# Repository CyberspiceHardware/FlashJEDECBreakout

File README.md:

# FlashJEDECBreakout

Allows use of SOIC packaged Flash chips in PDIP sockets for Flash, ROM, EPROM etc.

## Jumpers

There are two jumpers:

J1, selects how pin 1 (A14) of the flash part is connected, it can be either to
pin 1 of the header, pin 27 of the header, or omitted to tie it to ground (useful
for replacing 27C128 parts).

J2, selects how pin 26 (~WE) of the flash part is connected, it can be either to
pin 26 of the header, or to VDD.

## Parts list

- U1 - AT28C256E SOIC
- R1 - 3K3 0805 SMT
- J1 - 3 pin 0.1" header
- J2 - 3 pin 0.1" header
- CON1 - 2 x 14 way 0.1" double ended header

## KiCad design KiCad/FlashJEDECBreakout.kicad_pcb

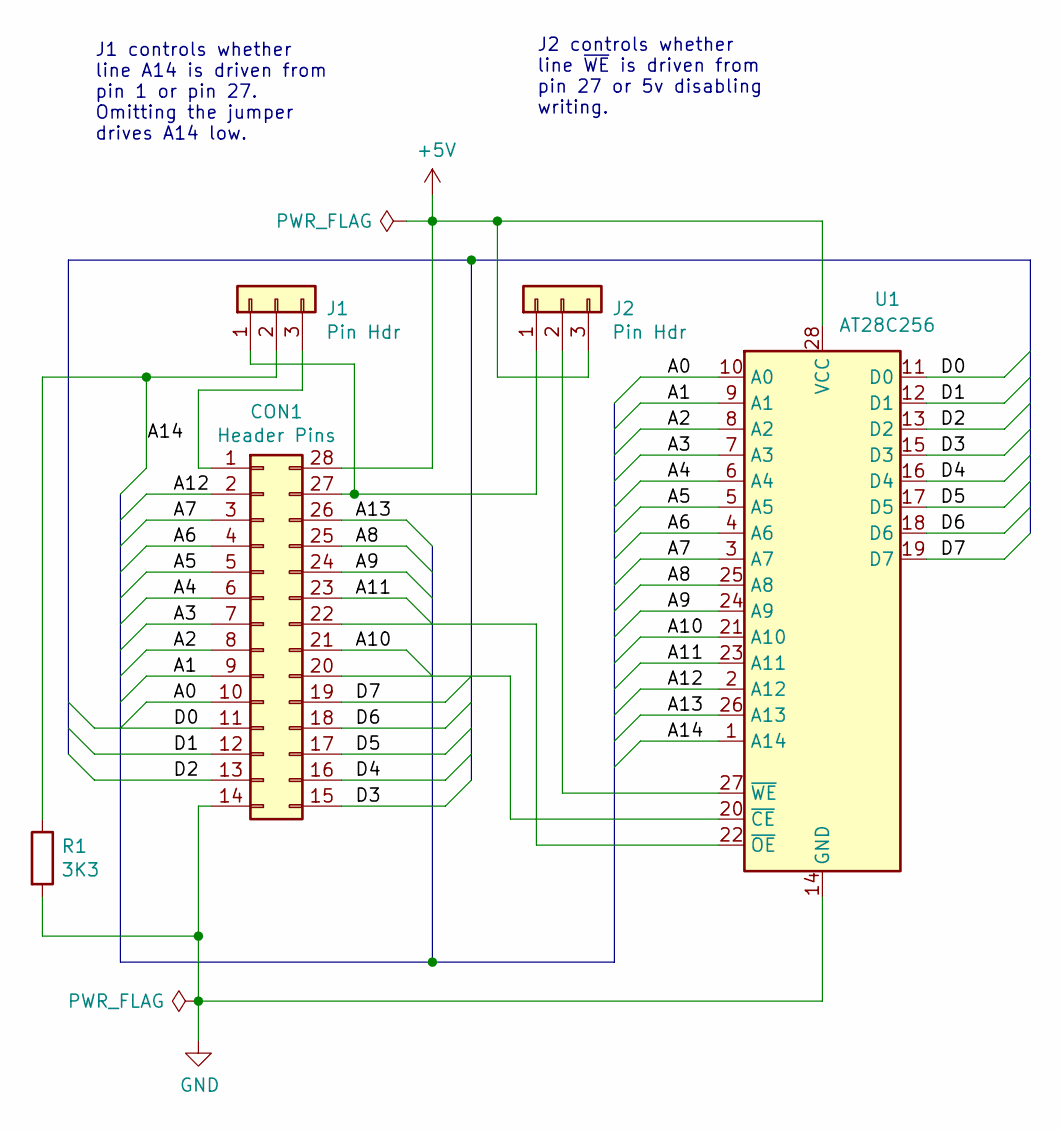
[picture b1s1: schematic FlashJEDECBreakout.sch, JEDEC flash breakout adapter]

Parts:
CON1: Header Pins; DIP-28_W15.24mm_Socket
J1, J2: Pin Hdr; PinHeader_1x03_P2.54mm_Vertical
R1: 3K3; R_0805_2012Metric_Pad1.20x1.40mm_HandSolder
U1: AT28C256; SOIC-28W_7.5x17.9mm_P1.27mm

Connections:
+5V: CON1.28, J2.3, U1.28 (VCC)
/A0: CON1.10, U1.10 (A0)
/A1: CON1.9, U1.9 (A1)
/A2: CON1.8, U1.8 (A2)
/A3: CON1.7, U1.7 (A3)
/A4: CON1.6, U1.6 (A4)
/A5: CON1.5, U1.5 (A5)
/A6: CON1.4, U1.4 (A6)
/A7: CON1.3, U1.3 (A7)
/A8: CON1.25, U1.25 (A8)
/A9: CON1.24, U1.24 (A9)
/A10: CON1.21, U1.21 (A10)
/A11: CON1.23, U1.23 (A11)
/A12: CON1.2, U1.2 (A12)
/A13: CON1.26, U1.26 (A13)
/A14: J1.2, R1.1, U1.1 (A14)
/D0: CON1.11, U1.11 (D0)
/D1: CON1.12, U1.12 (D1)
/D2: CON1.13, U1.13 (D2)
/D3: CON1.15, U1.15 (D3)
/D4: CON1.16, U1.16 (D4)
/D5: CON1.17, U1.17 (D5)
/D6: CON1.18, U1.18 (D6)
/D7: CON1.19, U1.19 (D7)
GND: CON1.14, R1.2, U1.14 (GND)
unnamed: CON1.1, J1.3
unnamed: CON1.20, U1.20 (~CE)
unnamed: CON1.22, U1.22 (~OE)
unnamed: CON1.27, J1.1, J2.1
unnamed: J2.2, U1.27 (~WE)

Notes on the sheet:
J1 controls whether line A14 is driven from pin 1 or pin 27. Omitting the jumper drives A14 low.
J2 controls whether line ~WE is driven from pin 27 or 5v disabling writing.

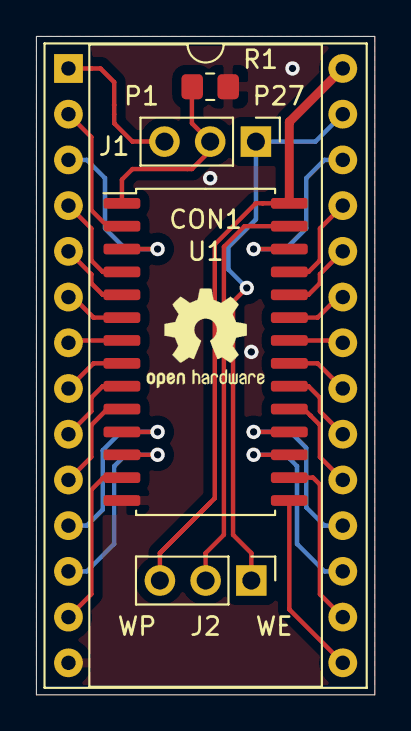
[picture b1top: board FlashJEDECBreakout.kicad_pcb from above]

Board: 2 copper layers, 18.8 x 36.6 mm, 5 parts (0 on the bottom side), 30 nets.

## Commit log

2022-04-23 Rev 1 version

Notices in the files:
KiCad/FlashJEDECBreakout.kicad_pcb:
(c) 2022 Cyberspice
KiCad/FlashJEDECBreakout.sch:
MIT License
